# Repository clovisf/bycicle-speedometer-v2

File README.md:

A bicycle odometer using a WiFi ESP-12 chip, reading speed on the wheel via a reed switch. More at https://fritzenlab.net/bicycle-odometer-with-esp-12/

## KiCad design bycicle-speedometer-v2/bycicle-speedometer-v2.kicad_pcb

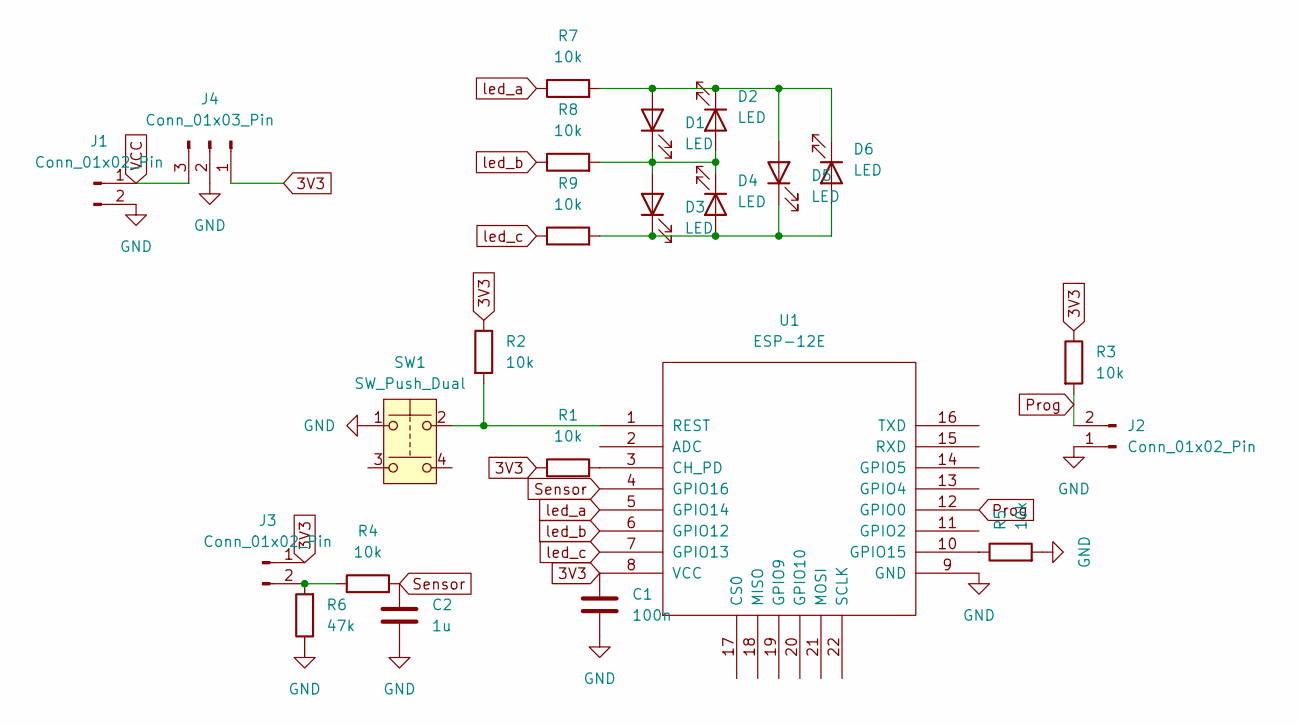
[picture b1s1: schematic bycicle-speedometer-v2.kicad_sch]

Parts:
C1: 100n; C_0805_2012Metric
C2: 1u; C_0805_2012Metric
D1, D2, D3, D4, D5, D6: LED; LED_D5.0mm
J1, J3: Conn_01x02_Pin; TerminalBlock_Phoenix_MKDS-1,5-2-5.08_1x02_P5.08mm_Horizont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
J2: Conn_01x02_Pin; PinHeader_1x02_P2.54mm_Vertical
J4: Conn_01x03_Pin; PinHeader_1x03_P2.54mm_Vertical
R1, R2, R3, R4, R5, R7, R8, R9: 10k; R_0805_2012Metric
R6: 47k; R_0805_2012Metric
SW1: SW_Push_Dual; SW_PUSH_6mm
U1: ESP-12E

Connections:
3V3: C1.1, J3.1, J4.1, R1.1, R2.1, R3.1, U1.8 (VCC)
GND: C1.2, C2.2, J1.2, J2.1, J4.2, R5.2, R6.1, SW1.1, U1.9 (GND)
unnamed: D1.2 (A), D2.1 (K), D5.2 (A), D6.1 (K), R7.2
unnamed: D1.1 (K), D2.2 (A), D3.2 (A), D4.1 (K), R8.2
unnamed: D3.1 (K), D4.2 (A), D5.1 (K), D6.2 (A), R9.2
unnamed: J3.2, R4.1, R6.2
unnamed: R1.2, U1.3 (CH_PD)
unnamed: R5.1, U1.10 (GPIO15)
unnamed: R2.2, SW1.2, U1.1 (REST)
Prog: J2.2, R3.2, U1.12 (GPIO0)
Sensor: C2.1, R4.2, U1.4 (GPIO16)
VCC: J1.1, J4.3
led_a: R7.1, U1.5 (GPIO14)
led_b: R8.1, U1.6 (GPIO12)
led_c: R9.1, U1.7 (GPIO13)

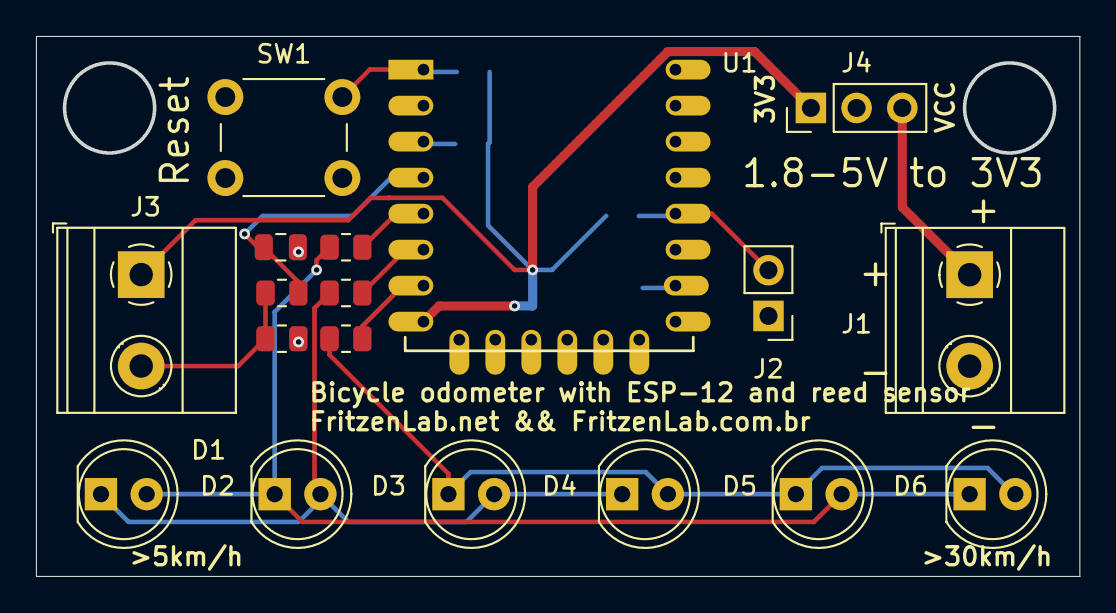
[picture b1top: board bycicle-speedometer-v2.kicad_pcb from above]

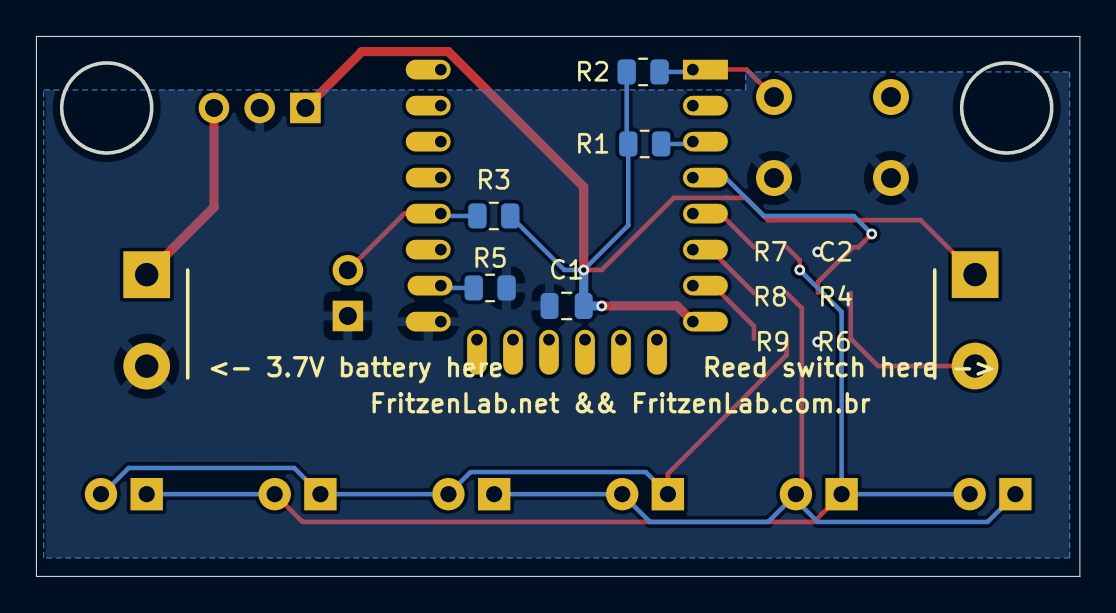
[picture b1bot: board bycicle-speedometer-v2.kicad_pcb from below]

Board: 2 copper layers, 57.8 x 29.9 mm, 23 parts (5 on the bottom side), 15 nets.

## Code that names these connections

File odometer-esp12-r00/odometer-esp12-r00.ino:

// First thing, install the ESP8266 support on the Arduino IDE,
// with a link from here https://blog.eletrogate.com/nodemcu-esp12-usando-arduino-ide-2/

// board pinout for Wemos D1 https://forum.arduino.cc/t/weird-wemos-d1-r1/920394/29?page=2
// board pinout for NodeMCU V3 https://cyberblogspot.com/nodemcu-v3-esp8266-pinout-and-configuration/

#include <ESP8266WiFi.h> // just to turn WiFi off, info from here https://arduino.stackexchange.com/questions/43376/can-the-wifi-on-esp8266-be-disabled

// for light sleep woken by a GPIO, I used this reference https://efcomputer.net.au/blog/esp8266-light-sleep-mode/
// there is also something here https://kevinstadler.github.io/notes/esp8266-deep-sleep-light-sleep-arduino/

#define led_a 14 // charlieplex pin 1
#define led_b 12 // charlieplex pin 2
#define led_c 13 // charlieplex pin 3
#define sensor 16 // reed sensor

// Required for LIGHT_SLEEP_T delay mode
/*extern "C" {
  #include "user_interface.h"
  #include "gpio.h"
}*/

long currenttime;
long oldtime;
int sleepcounter; 
bool previoussensorstatus;
long timeelapsed;
long previoustime;
float speedms;
float speedkmh;
float wheelperimeter= 2.0 * 3.14159265 * 0.365; // perimeter= 2 * pi * radius
int calldisplaycounter;
int requiredled;
int zerospeedcounter;
int callserialprint;
int contador; 

/*void light_sleep(){
   wifi_station_disconnect();
   wifi_set_opmode_current(NULL_MODE);
   wifi_fpm_set_sleep_type(LIGHT_SLEEP_T); // set sleep type, the above    posters wifi_set_sleep_type() didnt seem to work for me although it did let me compile and upload with no errors 
   wifi_fpm_open(); // Enables force sleep
   gpio_pin_wakeup_enable(GPIO_ID_PIN(4), GPIO_PIN_INTR_HILEVEL); // GPIO_ID_PIN(2) corresponds to GPIO2 on ESP8266-01 , GPIO_PIN_INTR_HILEVEL for a logic HIGH, can also do other interrupts, see gpio.h above
   //gpio_pin_wakeup_enable(4, GPIO_PIN_INTR_HILEVEL);
   wifi_fpm_do_sleep(0xFFFFFFF); // Sleep for longest possible time
 }*/

void ledon(int requiredled){
  //Serial.println("entrei");
  switch (requiredled) {
  case 0:
    pinMode(led_a, INPUT);
    pinMode(led_b, INPUT);
    pinMode(led_c, INPUT);
    //digitalWrite(led_a, LOW);
    //digitalWrite(led_b, LOW);
    //digitalWrite(led_c, LOW);
    break;
  case 1:
    pinMode(led_a, OUTPUT);
    pinMode(led_b, OUTPUT);
    pinMode(led_c, INPUT);
    digitalWrite(led_a, HIGH);
    digitalWrite(led_b, LOW);
    //digitalWrite(led_c, LOW);
    break;
  case 2:
    pinMode(led_a, OUTPUT);
    pinMode(led_b, OUTPUT);
    pinMode(led_c, INPUT);
    digitalWrite(led_a, LOW);
    digitalWrite(led_b, HIGH);
    //digitalWrite(led_c, LOW);
    break;
  case 3:
    pinMode(led_a, INPUT);
    pinMode(led_b, OUTPUT);
    pinMode(led_c, OUTPUT);
    //digitalWrite(led_a, LOW);
    digitalWrite(led_b, HIGH);
    digitalWrite(led_c, LOW);
    break;
  case 4:
    pinMode(led_a, INPUT);
    pinMode(led_b, OUTPUT);
    pinMode(led_c, OUTPUT);
    //digitalWrite(led_a, LOW);
    digitalWrite(led_b, LOW);
    digitalWrite(led_c, HIGH);
    break;
  case 5:
    pinMode(led_a, OUTPUT);
    pinMode(led_b, INPUT);
    pinMode(led_c, OUTPUT);
    digitalWrite(led_a, HIGH);
    //digitalWrite(led_b, LOW);
    digitalWrite(led_c, LOW);
    break;
  case 6:
    pinMode(led_a, OUTPUT);
    pinMode(led_b, INPUT);
    pinMode(led_c, OUTPUT);
    digitalWrite(led_a, LOW);
    //digitalWrite(led_b, LOW);
    digitalWrite(led_c, HIGH);
    break;
  default:
    // comando(s)
    break;
}
}
void setup() {
  // put your setup code here, to run once:
  Serial.begin(9600);

  WiFiMode(WIFI_STA);
  WiFi.disconnect(); 
  WiFi.mode(WIFI_OFF);
  WiFi.forceSleepBegin();
  delay(100);
    
  pinMode(sensor, INPUT);
  //gpio_init();
  
}

void loop() {
  // put your main code here, to run repeatedly:
  
  currenttime= micros();
  if(currenttime - oldtime > 5000){ //verifies the sensor every 5ms
    oldtime= micros(); // after 5ms have passed, reset the time counter
    zerospeedcounter++;
    if(zerospeedcounter > 600){ // if more than three seconds have passed without sensor detection (less than an avarage of 3km/h)
      speedkmh= 0; // zero the speed variables
      speedms= 0;
      timeelapsed= 0; // zero the last elapsed time
    }
    if(digitalRead(sensor) && !previoussensorstatus){ // if sensor is HIGH and just was LOW
      zerospeedcounter= 0; // if the sensor was detected within 3 seconds, zero the zero speed flag
      timeelapsed= millis() - previoustime; // calculates the elapsed time between now and the last sensor state change
      speedms= wheelperimeter / (timeelapsed / 1000.0); // THIS calculates speed, wheel perimeter over time elapsed between sensor detections. Dividing by 1000 to get seconds
      speedkmh= speedms * 3.6; // converts m/s to km/h and rounds it for displaying
      previoustime= millis(); // reset the previoustime variable to the current millis()
      previoussensorstatus= true; // when the sensor goes to HIGH this variables goes too
    }else if(!digitalRead(sensor) && previoussensorstatus){ // if sensor is LOW and just was HIGH
      previoussensorstatus= false; // when the sensor goes LOW, reset this variable
    }
    // function to call and light the LED display
    calldisplaycounter++;
    if(calldisplaycounter == 50){ // every 250ms
      calldisplaycounter= 0;

      if(speedkmh >= 30){
        ledon(6);
      }else if(speedkmh >= 25){
        ledon(5);
      }else if(speedkmh >= 20){
        ledon(4);
      }else if(speedkmh>= 15){
        ledon(3);
      }else if(speedkmh >= 10){
        ledon(2);
      }else if(speedkmh >= 5){
        ledon(1);
      }else{
        ledon(0);
      }
    }
    /*callserialprint++;
    if(callserialprint == 100){
      callserialprint= 0;
      Serial.println(timeelapsed); 
    }*/
  }  
}

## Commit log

2024-06-12 added first schematic attempt
2024-06-14 initiated schematic update
2024-06-14 modified schematic
2024-06-19 schematic edited a bit
2024-06-19 schematic edited
2024-06-20 edited schematic diagram
2024-06-21 edited schematics
2024-06-21 created fabrication files
2024-06-21 backups
2024-07-02 just backup files
2024-07-02 removing backups
2024-07-29 added images
2024-07-31 added images and videos
